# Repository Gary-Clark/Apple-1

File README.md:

# Apple-1

This is a project to mount a couple of EPROM's on the Apple-1 computer.

Gerbers for a simple PCB to mount two 2732 EPROMs selected via T & S select lines on the Apple-1 bus. If S is mapped to E000, BASIC can be burnt into the
EPROM meaning that BASIC is available without having to load from external storage.
The RAM normally located at E000 can then be mapped to the second bank of 4k giving more RAM for programs.

The .rar file contains the plot & drill files that can be uploaded to sites such as JCLPBC for production. The remaining files are Kicad files of the board.

Also included is a PCB for a two slot riser card so that the EPROM card and the Cassette interface can be fitted inside the case (given sufficient headroom). This card does not include any buffering but has been tested with an EPROM card and an ACI card installed.

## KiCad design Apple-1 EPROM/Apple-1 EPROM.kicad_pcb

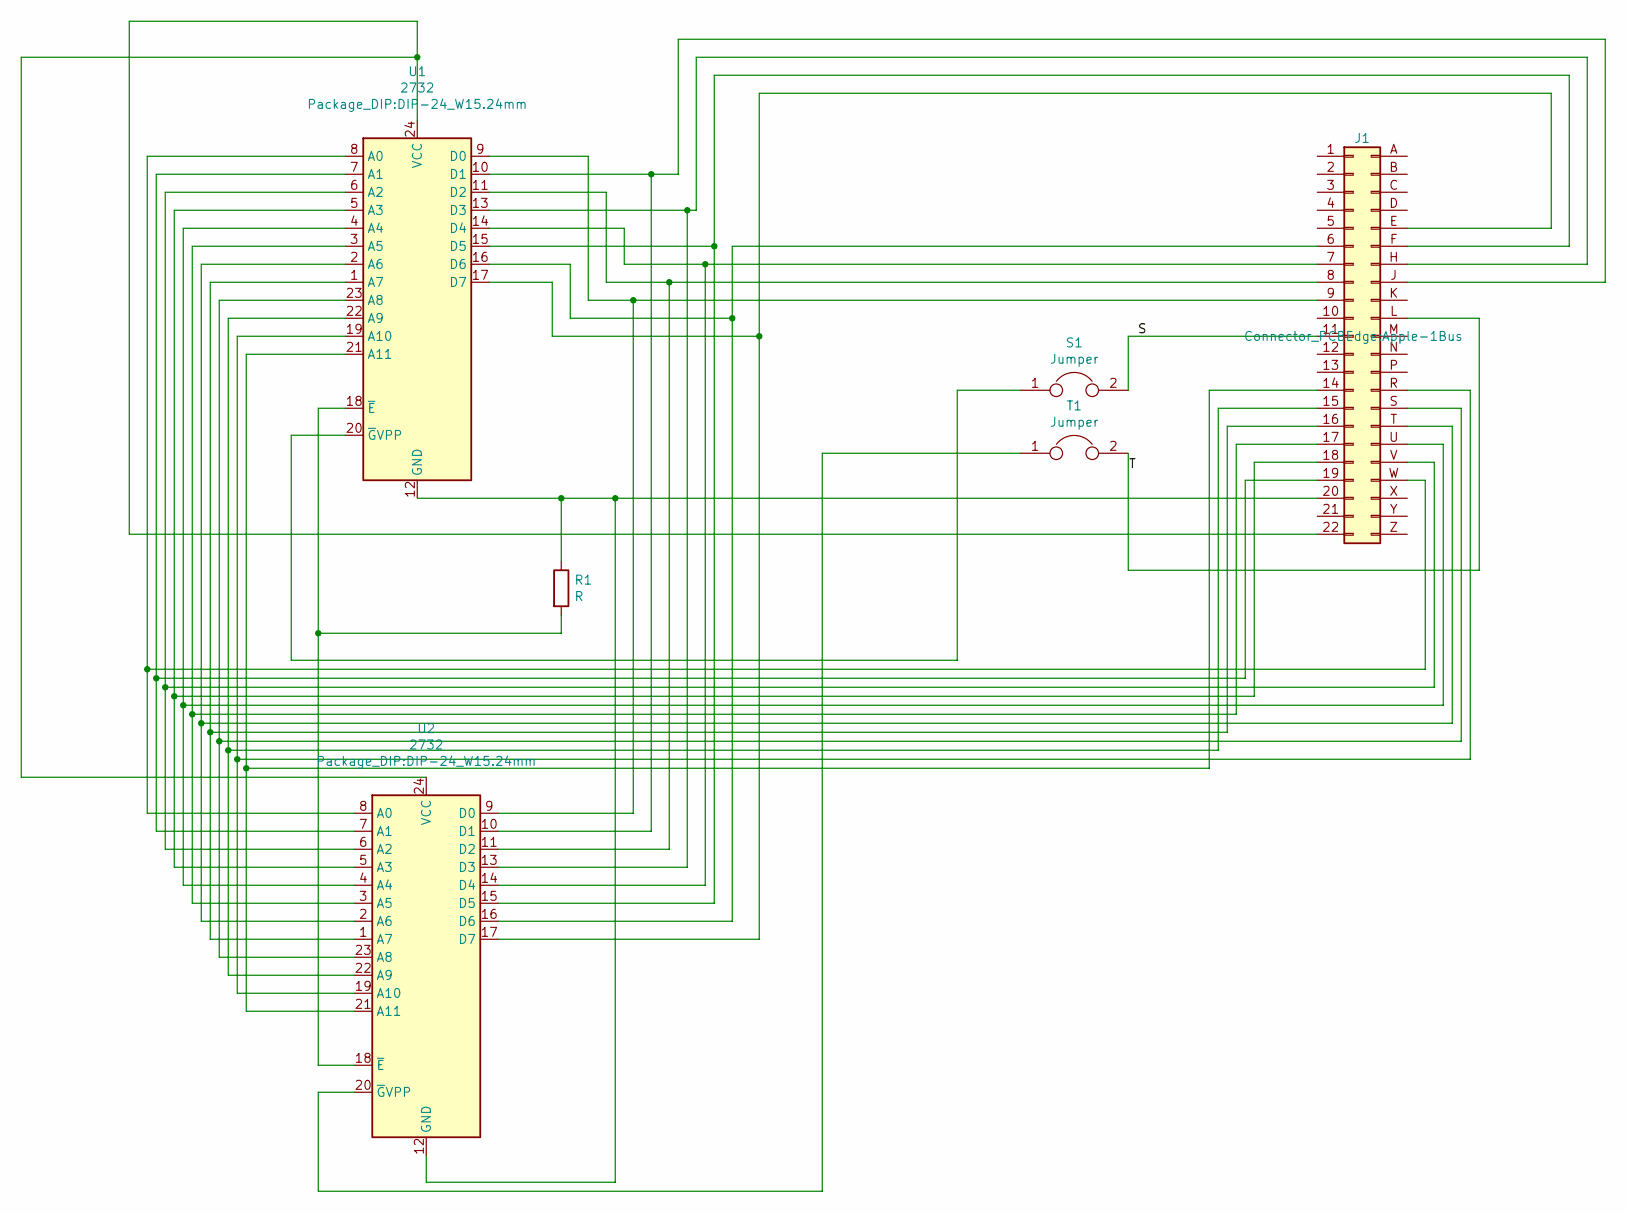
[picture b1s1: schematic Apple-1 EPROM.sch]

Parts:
J1: Conn_02x22_Apple_1-Connector_Generic_apple; Apple-1Bus
R1: R; R_Axial_DIN0411_L9.9mm_D3.6mm_P15.24mm_Horizontal
S1: Jumper; PinHeader_1x02_P2.54mm_Vertical
T1: Jumper; PinHeader_1x02_P2.54mm_Vertical
U1, U2: 2732; DIP-24_W15.24mm

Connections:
/S: J1.11, S1.2
/T: J1.L, T1.2
unnamed: J1.6, U1.16 (D6), U2.16 (D6)
unnamed: J1.7, U1.14 (D4), U2.14 (D4)
unnamed: J1.8, U1.11 (D2), U2.11 (D2)
unnamed: J1.9, U1.9 (D0), U2.9 (D0)
unnamed: J1.14, U1.21 (A11), U2.21 (A11)
unnamed: J1.15, U1.22 (A9), U2.22 (A9)
unnamed: J1.16, U1.1 (A7), U2.1 (A7)
unnamed: J1.17, U1.3 (A5), U2.3 (A5)
unnamed: J1.18, U1.5 (A3), U2.5 (A3)
unnamed: J1.19, U1.7 (A1), U2.7 (A1)
unnamed: J1.20, R1.1, U1.12 (GND), U2.12 (GND)
unnamed: J1.22, U1.24 (VCC), U2.24 (VCC)
unnamed: J1.E, U1.17 (D7), U2.17 (D7)
unnamed: J1.F, U1.15 (D5), U2.15 (D5)
unnamed: J1.H, U1.13 (D3), U2.13 (D3)
unnamed: J1.J, U1.10 (D1), U2.10 (D1)
unnamed: J1.R, U1.19 (A10), U2.19 (A10)
unnamed: J1.S, U1.23 (A8), U2.23 (A8)
unnamed: J1.T, U1.2 (A6), U2.2 (A6)
unnamed: J1.U, U1.4 (A4), U2.4 (A4)
unnamed: J1.V, U1.6 (A2), U2.6 (A2)
unnamed: J1.W, U1.8 (A0), U2.8 (A0)
unnamed: R1.2, U1.18 (~E), U2.18 (~E)
unnamed: S1.1, U1.20 (~G~VPP)
unnamed: T1.1, U2.20 (~G~VPP)

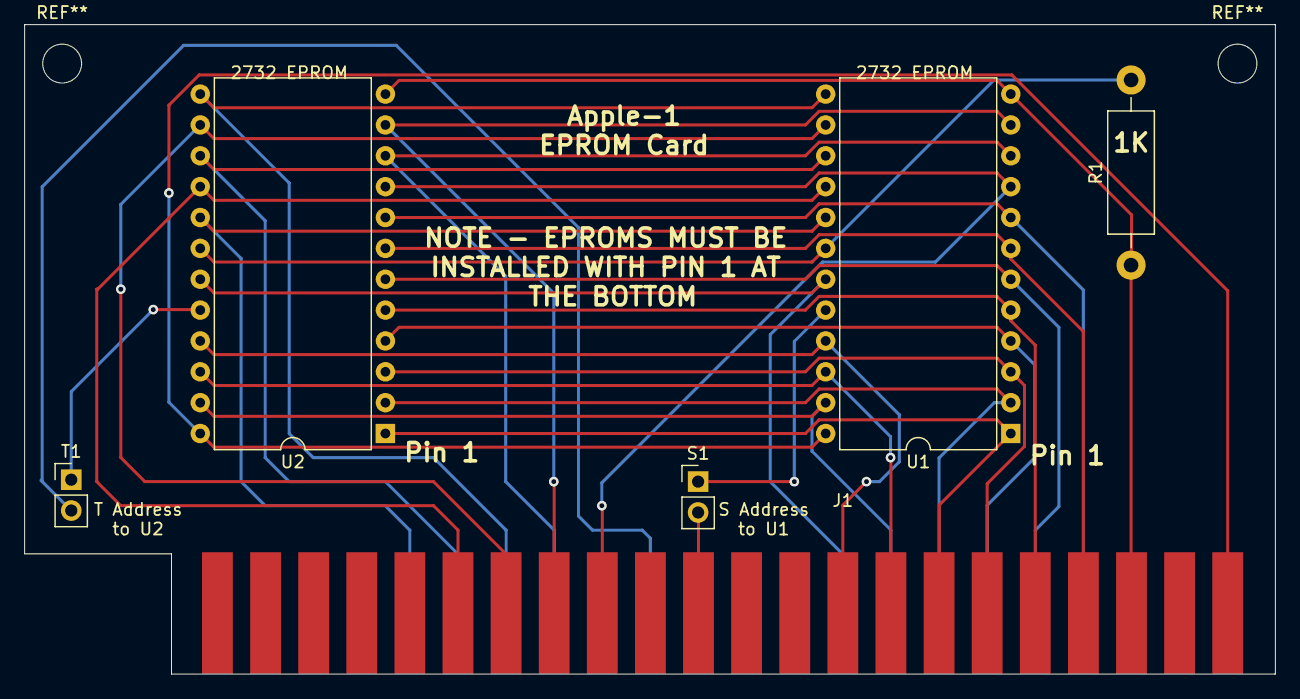
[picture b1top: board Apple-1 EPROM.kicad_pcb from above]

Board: 2 copper layers, 103.0 x 53.5 mm, 6 parts (0 on the bottom side), 27 nets.

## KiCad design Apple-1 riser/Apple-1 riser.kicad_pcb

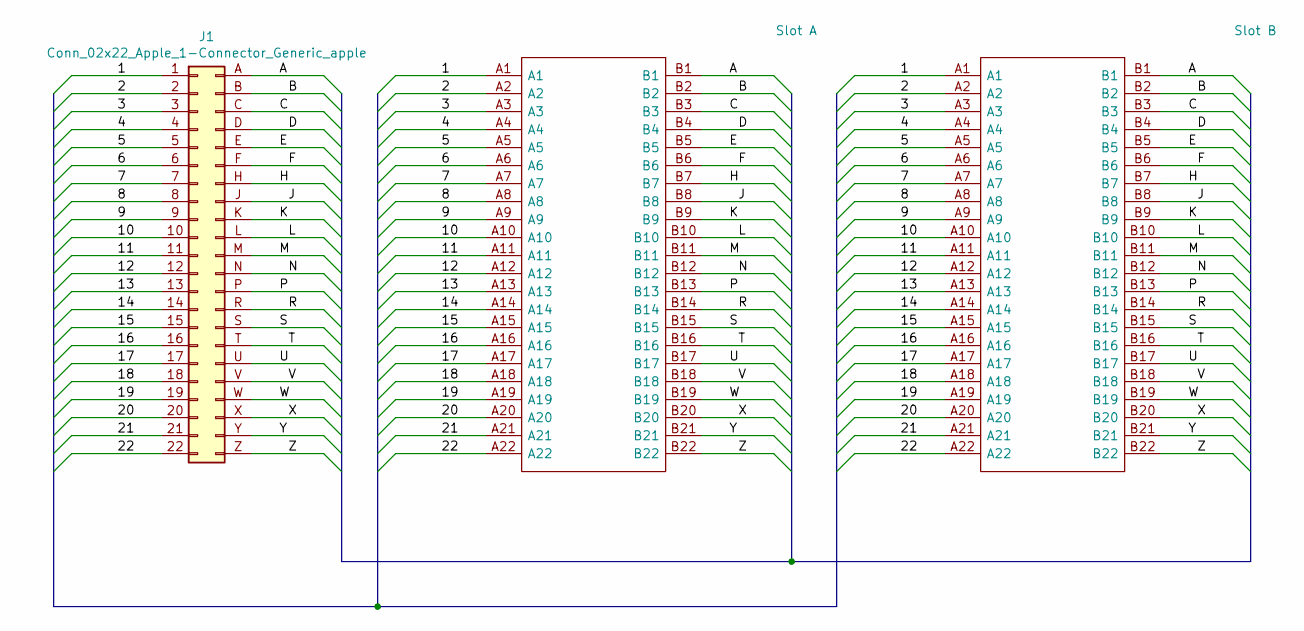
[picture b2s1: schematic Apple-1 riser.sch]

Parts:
J1: Conn_02x22_Apple_1-Connector_Generic_apple; Apple-1Bus
J2: Slot A; 305044521201; Manufacturer_Part_Number 305-044-521-201; Mouser Part Number 587-305-044-521-201
J3: Slot B; 305044521201; Manufacturer_Part_Number 305-044-521-201; Mouser Part Number 587-305-044-521-201

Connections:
/1: J1.1 (RF), J2.A1, J3.A1
/2: J1.2, J2.A2, J3.A2
/3: J1.3, J2.A3, J3.A3
/4: J1.4, J2.A4, J3.A4
/5: J1.5, J2.A5, J3.A5
/6: J1.6, J2.A6, J3.A6
/7: J1.7, J2.A7, J3.A7
/8: J1.8, J2.A8, J3.A8
/9: J1.9, J2.A9, J3.A9
/10: J1.10, J2.A10, J3.A10
/11: J1.11, J2.A11, J3.A11
/12: J1.12, J2.A12, J3.A12
/13: J1.13, J2.A13, J3.A13
/14: J1.14, J2.A14, J3.A14
/15: J1.15, J2.A15, J3.A15
/16: J1.16, J2.A16, J3.A16
/17: J1.17, J2.A17, J3.A17
/18: J1.18, J2.A18, J3.A18
/19: J1.19, J2.A19, J3.A19
/20: J1.20, J2.A20, J3.A20
/21: J1.21, J2.A21, J3.A21
/22: J1.22, J2.A22, J3.A22
/A: J1.A, J2.B1, J3.B1
/B: J1.B, J2.B2, J3.B2
/C: J1.C, J2.B3, J3.B3
/D: J1.D, J2.B4, J3.B4
/E: J1.E, J2.B5, J3.B5
/F: J1.F, J2.B6, J3.B6
/H: J1.H, J2.B7, J3.B7
/J: J1.J, J2.B8, J3.B8
/K: J1.K, J2.B9, J3.B9
/L: J1.L, J2.B10, J3.B10
/M: J1.M, J2.B11, J3.B11
/N: J1.N, J2.B12, J3.B12
/P: J1.P, J2.B13, J3.B13
/R: J1.R, J2.B14, J3.B14
/S: J1.S, J2.B15, J3.B15
/T: J1.T, J2.B16, J3.B16
/U: J1.U, J2.B17, J3.B17
/V: J1.V, J2.B18, J3.B18
/W: J1.W, J2.B19, J3.B19
/X: J1.X, J2.B20, J3.B20
/Y: J1.Y, J2.B21, J3.B21
/Z: J1.Z, J2.B22, J3.B22

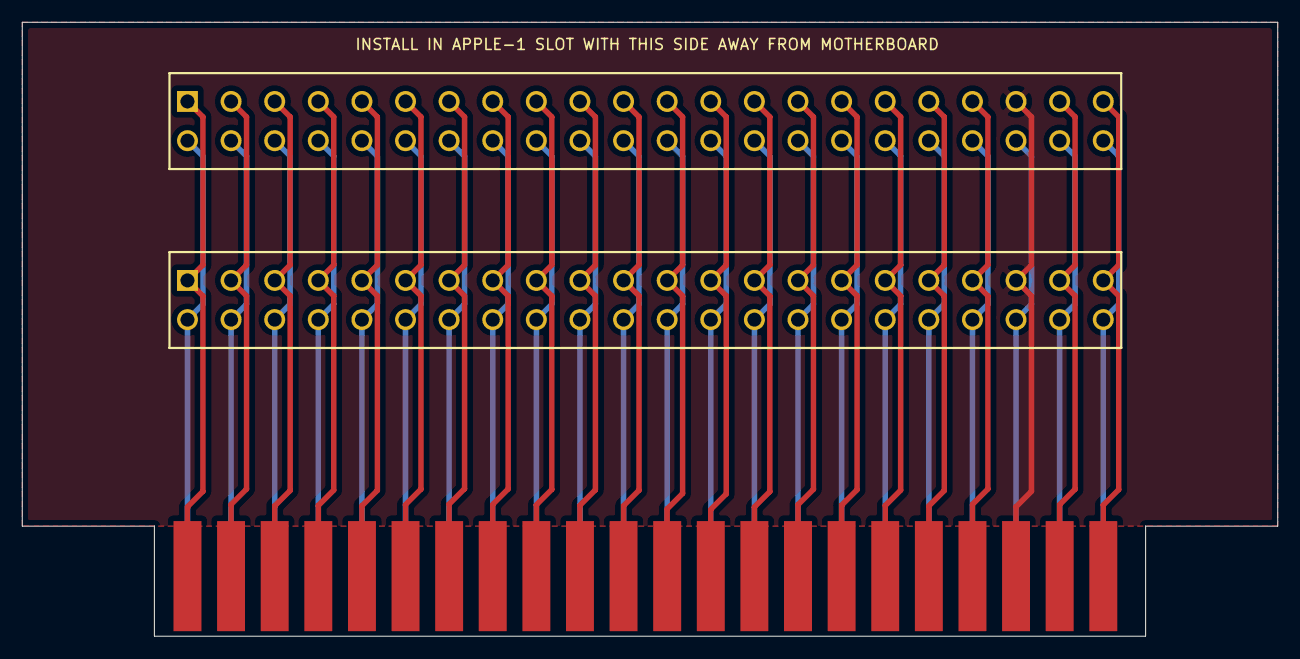
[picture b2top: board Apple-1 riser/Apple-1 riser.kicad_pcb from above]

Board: 2 copper layers, 114.0 x 55.8 mm, 3 parts (0 on the bottom side), 44 nets.

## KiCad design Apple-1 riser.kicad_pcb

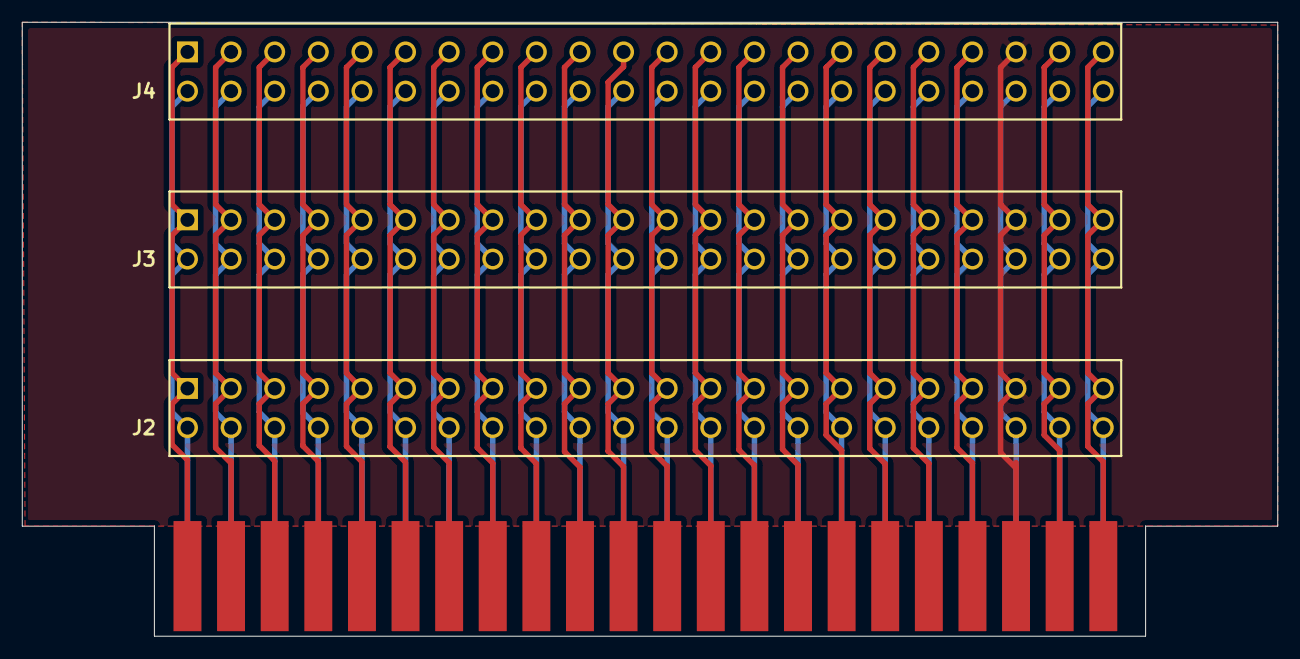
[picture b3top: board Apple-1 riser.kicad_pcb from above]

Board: 2 copper layers, 114.0 x 55.8 mm, 4 parts (0 on the bottom side), 44 nets.

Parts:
J1: Conn_02x22_Apple_1-Connector_Generic_apple; Apple-1Bus
J2: Slot A; 305044521201
J3: Slot B; 305044521201
J4: Slot C; 305044521201

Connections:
/1: J1.1, J2.A1, J3.A1, J4.A1
/2: J1.2, J2.A2, J3.A2, J4.A2
/3: J1.3, J2.A3, J3.A3, J4.A3
/4: J1.4, J2.A4, J3.A4, J4.A4
/5: J1.5, J2.A5, J3.A5, J4.A5
/6: J1.6, J2.A6, J3.A6, J4.A6
/7: J1.7, J2.A7, J3.A7, J4.A7
/8: J1.8, J2.A8, J3.A8, J4.A8
/9: J1.9, J2.A9, J3.A9, J4.A9
/10: J1.10, J2.A10, J3.A10, J4.A10
/11: J1.11, J2.A11, J3.A11, J4.A11
/12: J1.12, J2.A12, J3.A12, J4.A12
/13: J1.13, J2.A13, J3.A13, J4.A13
/14: J1.14, J2.A14, J3.A14, J4.A14
/15: J1.15, J2.A15, J3.A15, J4.A15
/16: J1.16, J2.A16, J3.A16, J4.A16
/17: J1.17, J2.A17, J3.A17, J4.A17
/18: J1.18, J2.A18, J3.A18, J4.A18
/19: J1.19, J2.A19, J3.A19, J4.A19
/20: J1.20, J2.A20, J3.A20, J4.A20
/21: J1.21, J2.A21, J3.A21, J4.A21
/22: J1.22, J2.A22, J3.A22, J4.A22
/A: J1.A, J2.B1, J3.B1, J4.B1
/B: J1.B, J2.B2, J3.B2, J4.B2
/C: J1.C, J2.B3, J3.B3, J4.B3
/D: J1.D, J2.B4, J3.B4, J4.B4
/E: J1.E, J2.B5, J3.B5, J4.B5
/F: J1.F, J2.B6, J3.B6, J4.B6
/H: J1.H, J2.B7, J3.B7, J4.B7
/J: J1.J, J2.B8, J3.B8, J4.B8
/K: J1.K, J2.B9, J3.B9, J4.B9
/L: J1.L, J2.B10, J3.B10, J4.B10
/M: J1.M, J2.B11, J3.B11, J4.B11
/N: J1.N, J2.B12, J3.B12, J4.B12
/P: J1.P, J2.B13, J3.B13, J4.B13
/R: J1.R, J2.B14, J3.B14, J4.B14
/S: J1.S, J2.B15, J3.B15, J4.B15
/T: J1.T, J2.B16, J3.B16, J4.B16
/U: J1.U, J2.B17, J3.B17, J4.B17
/V: J1.V, J2.B18, J3.B18, J4.B18
/W: J1.W, J2.B19, J3.B19, J4.B19
/X: J1.X, J2.B20, J3.B20, J4.B20
/Y: J1.Y, J2.B21, J3.B21, J4.B21
/Z: J1.Z, J2.B22, J3.B22, J4.B22
